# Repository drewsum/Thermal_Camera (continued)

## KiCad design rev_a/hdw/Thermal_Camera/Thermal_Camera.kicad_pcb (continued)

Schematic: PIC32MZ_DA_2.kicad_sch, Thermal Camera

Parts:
U1701: PIC32MZ2064DAR176; LQFP-176_20x20mm_P0.4mm_7p9x7p9mm_EP; Digi-Key PN PIC32MZ2064DAR176-I/2J-ND

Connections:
GLCD_B0: U1701.89 (GD16/EBID8/RPF5/SCL5/PMD8/RF5); also elsewhere on the board
GLCD_B1: U1701.97 (GD17/EBID9/RPF4/SDA5/PMD9/RF4); also elsewhere on the board
GLCD_B2: U1701.146 (GD18/EBIBS1/RJ10); also elsewhere on the board
GLCD_B3: U1701.130 (GD19/EBIA21/RK7); also elsewhere on the board
GLCD_B4: U1701.151 (GD20/EBIA22/RJ3); also elsewhere on the board
GLCD_B5: U1701.92 (GD21/EBIA23/RH15); also elsewhere on the board
GLCD_B7: U1701.137 (GD23/EBIA16/RK0); also elsewhere on the board
GLCD_G0: U1701.143 (GD8/EBID11/PMD11/RJ14); also elsewhere on the board
GLCD_G1: U1701.145 (GD9/EBIBS0/RJ12); also elsewhere on the board
GLCD_G4: U1701.134 (GD12/EBIA17/RK3); also elsewhere on the board
GLCD_G5: U1701.133 (GD13/EBIA18/RK4); also elsewhere on the board
GLCD_G6: U1701.132 (GD14/EBIA19/RK5); also elsewhere on the board
GLCD_G7: U1701.131 (GD15/EBIA20/RK6); also elsewhere on the board
GLCD_GCLK: U1701.148 (GCLK/EBICS2/RJ6); also elsewhere on the board
GLCD_GEN: U1701.147 (GEN/EBICS3/RJ7); also elsewhere on the board
GLCD_HSYNC: U1701.149 (HSYNC/EBICS1/RJ5); also elsewhere on the board
GLCD_R0: U1701.144 (GD0/EBID13/PMD13/RJ13); also elsewhere on the board
GLCD_R3: U1701.96 (GD3/EBIA8/RPG0/PMA8/RG0); also elsewhere on the board
GLCD_R4: U1701.95 (GD4/EBIA9/RPG1/PMA9/RG1); also elsewhere on the board
GLCD_R5: U1701.90 (GD5/EBIA10/RPF1/PMA10/RF1); also elsewhere on the board
GLCD_R6: U1701.91 (GD6/EBIA11/RPF0/PMA11/RF0); also elsewhere on the board
GLCD_VSYNC: U1701.150 (VSYNC/EBICS0/RJ4); also elsewhere on the board
LCD _CTP_RESET: U1701.112 (ETXD1/RJ9); also elsewhere on the board
LCD_CTP_INT: U1701.113 (ETXD0/RJ8); also elsewhere on the board
LCD_ENABLE: U1701.111 (ERXCLK/EREFCLK/RJ11); also elsewhere on the board
PGOOD_LED_SHDN: U1701.106 (ECOL/RH10); also elsewhere on the board
POS1P2_PGOOD: U1701.105 (ECRS/RH12); also elsewhere on the board
POS1P2_RUN: U1701.104 (ERXDV/ECRSDV/RH13); also elsewhere on the board
POS1P8_PGOOD: U1701.139 (EBIA4/AN36/PMA4/RH7); also elsewhere on the board
POS2P8_PGOOD: U1701.108 (ERXD0/RH8); also elsewhere on the board
POS2P8_RUN: U1701.107 (ERXD3/RH9); also elsewhere on the board
POS3P0_PGOOD: U1701.101 (ERXD2/RH6); also elsewhere on the board
POS12_PGOOD: U1701.100 (ERXD1/RH5); also elsewhere on the board
SDHC_SDDATA0: U1701.64 (TRD0/SDDATA0/SQID0/RG13); also elsewhere on the board
SDHC_SDDATA1: U1701.56 (TRD1/SDDATA1/SQID1/RG12); also elsewhere on the board
SDHC_SDDATA2: U1701.65 (TRD2/SDDATA2/SQID2/RG14); also elsewhere on the board
SD_PWR_EN: U1701.34 (AN21/RG15); also elsewhere on the board
SD_SPI_MISO: U1701.31 (AN13/C1INC/RPG7/SDA4/RG7); also elsewhere on the board
SD_SPI_MOSI: U1701.32 (AN30/C2IND/RPG8/SCL4/RG8); also elsewhere on the board
SD_SPI_SCK: U1701.30 (AN14/C1IND/SCK2/RG6); also elsewhere on the board
~SDHC_SDWP: U1701.141 (SDWP/EBIRP/RH2); also elsewhere on the board
~SD_SPI_CS: U1701.33 (EBIA2/AN23/C2INC/RPG9/PMA2/RG9); also elsewhere on the board

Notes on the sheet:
GLCD_G7
GPIO
GLCD_GEN
GLCD_VSYNC
GLCD_B0
GLCD_R6
GLCD_G0
SDDATA0
GLCD_HSYNC
GLCD_B4
GLCD_GCLK
GLCD_G6
SDDATA2
GLCD_B5
GLCD_R0
GLCD_B1
SDI2
GLCD_G4
GLCD_R3
GLCD_R4
SCK2
SDWP
See TABLE 36-1:RGB COLOR MAPPING for Graphic LCD Pin Mapping
SDDATA1
GLCD_G5
SDO2
GLCD_R5
GLCD_B7
GLCD_B3
GLCD_G1
GLCD_B2

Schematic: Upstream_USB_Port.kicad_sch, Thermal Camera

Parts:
C2601, C2603, C2605: 10uF; C_0402; Voltage 10V; Digi-Key PN 490-GRM155R61A106ME11DCT-ND
C2602: 0.1uF; C_0402; Voltage 50V; Digi-Key PN 490-10697-1-ND
C2604, C2606: 22pF; C_0402; Voltage 50V; Digi-Key PN 490-5868-1-ND
C2607: 10uF; C_1206; Voltage 25V; Digi-Key PN 399-8153-1-ND
J2601: USB_B_Mini; USB_Mini-B; Digi-Key PN 732-2109-1-ND
R2601: 10k; R_0402; Tolerance 1%; Digi-Key PN RMCF0402FT10K0CT-ND
R2602, R2603: 27; R_0402; Tolerance 1%; Digi-Key PN RMCF0402FT27R0CT-ND
R2604: 3.57k; R_0402; Tolerance 1%; Digi-Key PN RMCF0402FT3K57CT-ND
R2605: 1.15k; R_0402; Tolerance 1%; Digi-Key PN RMCF0402FT1K15CT-ND
R2606: 1.5k; R_0402; Tolerance 1%; Digi-Key PN RMCF0402FT1K50CT-ND
TP2601, TP2602: TP; Test_Point
U2601: TPS7A92; Texas_S-PDSO-N10_EP1.2x2mm; Digi-Key PN TPS7A9201DSKR
U2602: TPD3S044DBVR; SOT-23-6; Digi-Key PN 296-38836-1-ND

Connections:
+3.3V_USB: C2603.1, C2605.1, R2601.1, R2604.1, R2606.1, TP2601.1 (TP), U2601.1 (OUT), U2601.2 (OUT); also elsewhere on the board
+5V_USB: C2601.1, C2607.1, TP2602.1 (TP), U2601.7 (EN), U2601.9 (IN), U2601.10 (IN), U2602.4 (OUT); also elsewhere on the board
/Upstream USB Port/UFP_USB_CONN_USB+: J2601.3 (D+), R2602.1
/Upstream USB Port/UFP_USB_CONN_USB-: J2601.2 (D-), R2603.1
CHASSIS: J2601.6 (Shield)
GND: C2601.2, C2602.2, C2603.2, C2604.2, C2605.2, C2606.2, C2607.2, J2601.5 (GND), R2605.2, U2601.4 (GND), U2601.6 (SS_CTRL), U2601.11 (GND), U2602.2 (GND); also elsewhere on the board
unnamed: J2601.1 (VBUS), U2602.1 (EN), U2602.3 (IN)
unnamed: R2604.2, R2605.1, U2601.3 (FB)
unnamed: C2602.1, U2601.8 (NR/SS)
POS3P3_USB_PGOOD: R2601.2, U2601.5 (PG); also elsewhere on the board
UFP_USB_D+: C2604.1, R2602.2, R2606.2, U2602.6 (D1); also elsewhere on the board
UFP_USB_D-: C2606.1, R2603.2, U2602.5 (D2); also elsewhere on the board

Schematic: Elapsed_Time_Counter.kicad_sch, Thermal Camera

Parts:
C2301, C2302, C2303: 10uF; C_0402; Voltage 10V; Digi-Key PN 490-GRM155R61A106ME11DCT-ND
C2304, C2305: 0.1uF; C_0402; Voltage 50V; Digi-Key PN 490-10697-1-ND
D2301: BAT48JFILM; D_SOD-323; Digi-Key PN 497-5711-1-ND
DOC2301: 0x6B
DOC2302: 0x1F
U2301: DS1683; SOIC-8_3.9x4.9mm_Pitch1.27mm; Digi-Key PN DS1683S+-ND
U2302: MCP9804; DFN-8-1EP_3x2mm_P0.5mm_EP1.3x1.5mm; Digi-Key PN MCP9804T-E/MCCT-ND

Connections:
+3.0V: C2305.1, D2301.2 (A), U2301.1 (EVENT), U2302.5 (A2), U2302.6 (A1), U2302.7 (A0), U2302.8 (V_{DD}); also elsewhere on the board
GND: C2301.2, C2302.2, C2303.2, C2304.2, C2305.2, U2301.4 (GND), U2302.4 (GND), U2302.9 (EP/GND); also elsewhere on the board
I2C_SCL: U2301.5 (SCL), U2302.2 (SCL); also elsewhere on the board
I2C_SDA: U2301.6 (SDA), U2302.1 (SDA); also elsewhere on the board
unnamed: C2301.1, C2302.1, C2303.1, C2304.1, D2301.1 (K), U2301.8 (VCC)

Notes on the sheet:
Ambient, place away from power components

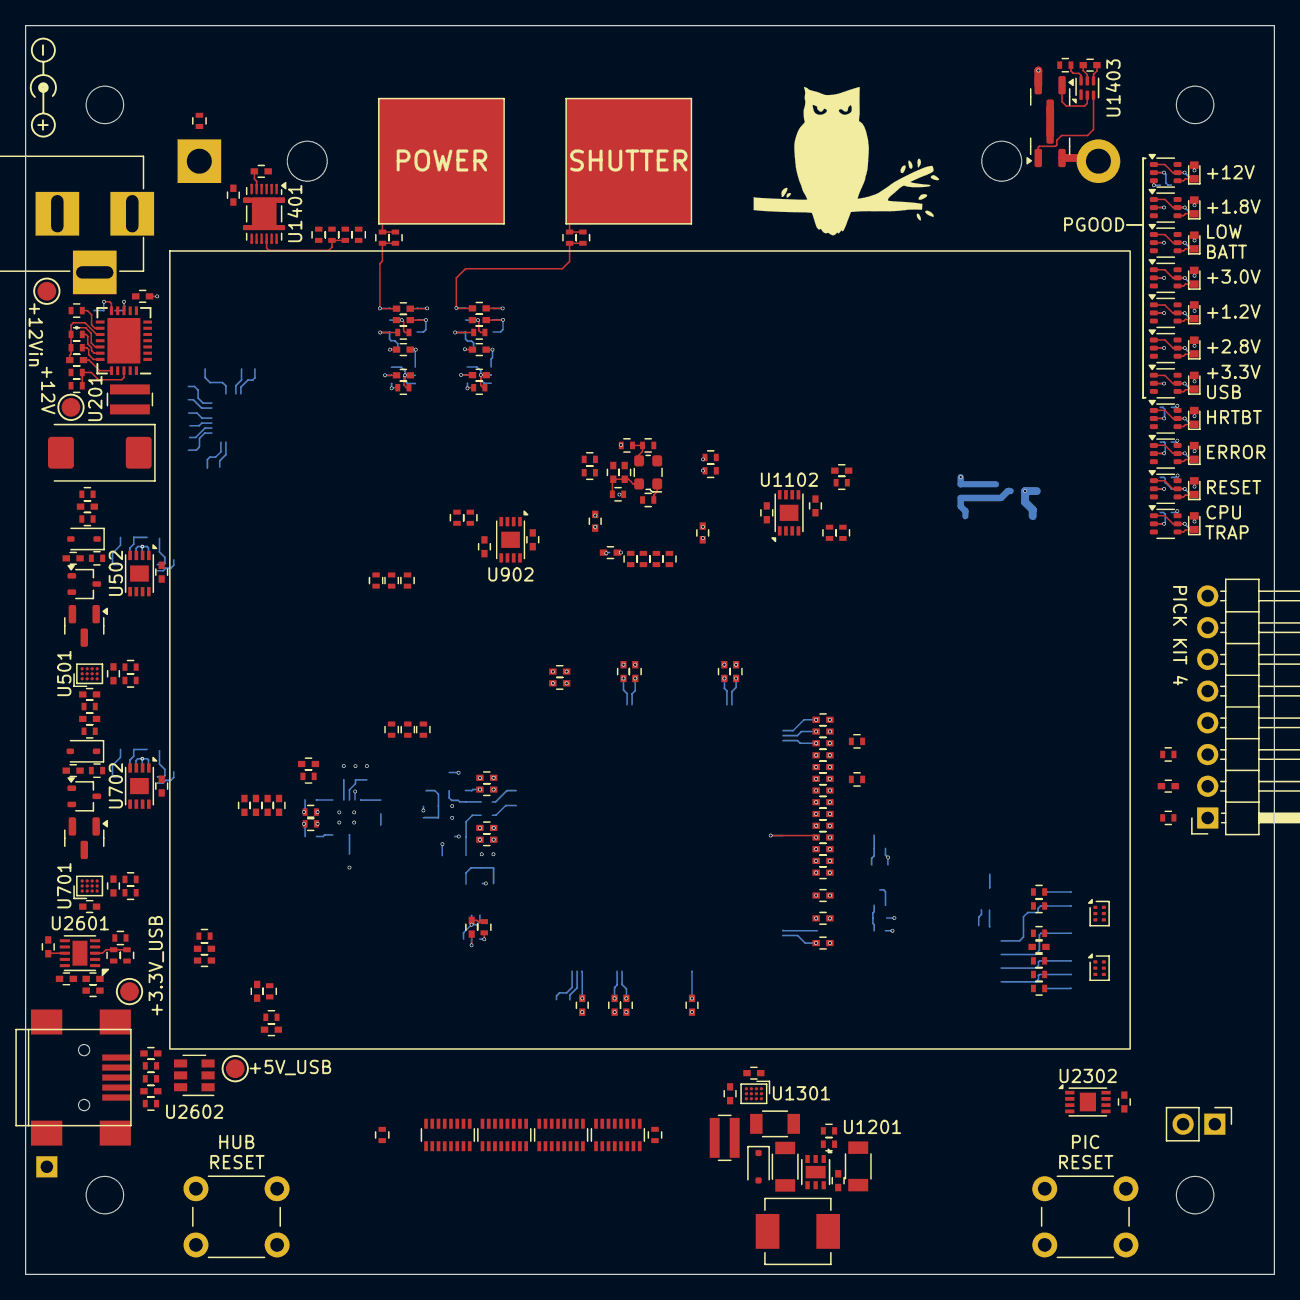
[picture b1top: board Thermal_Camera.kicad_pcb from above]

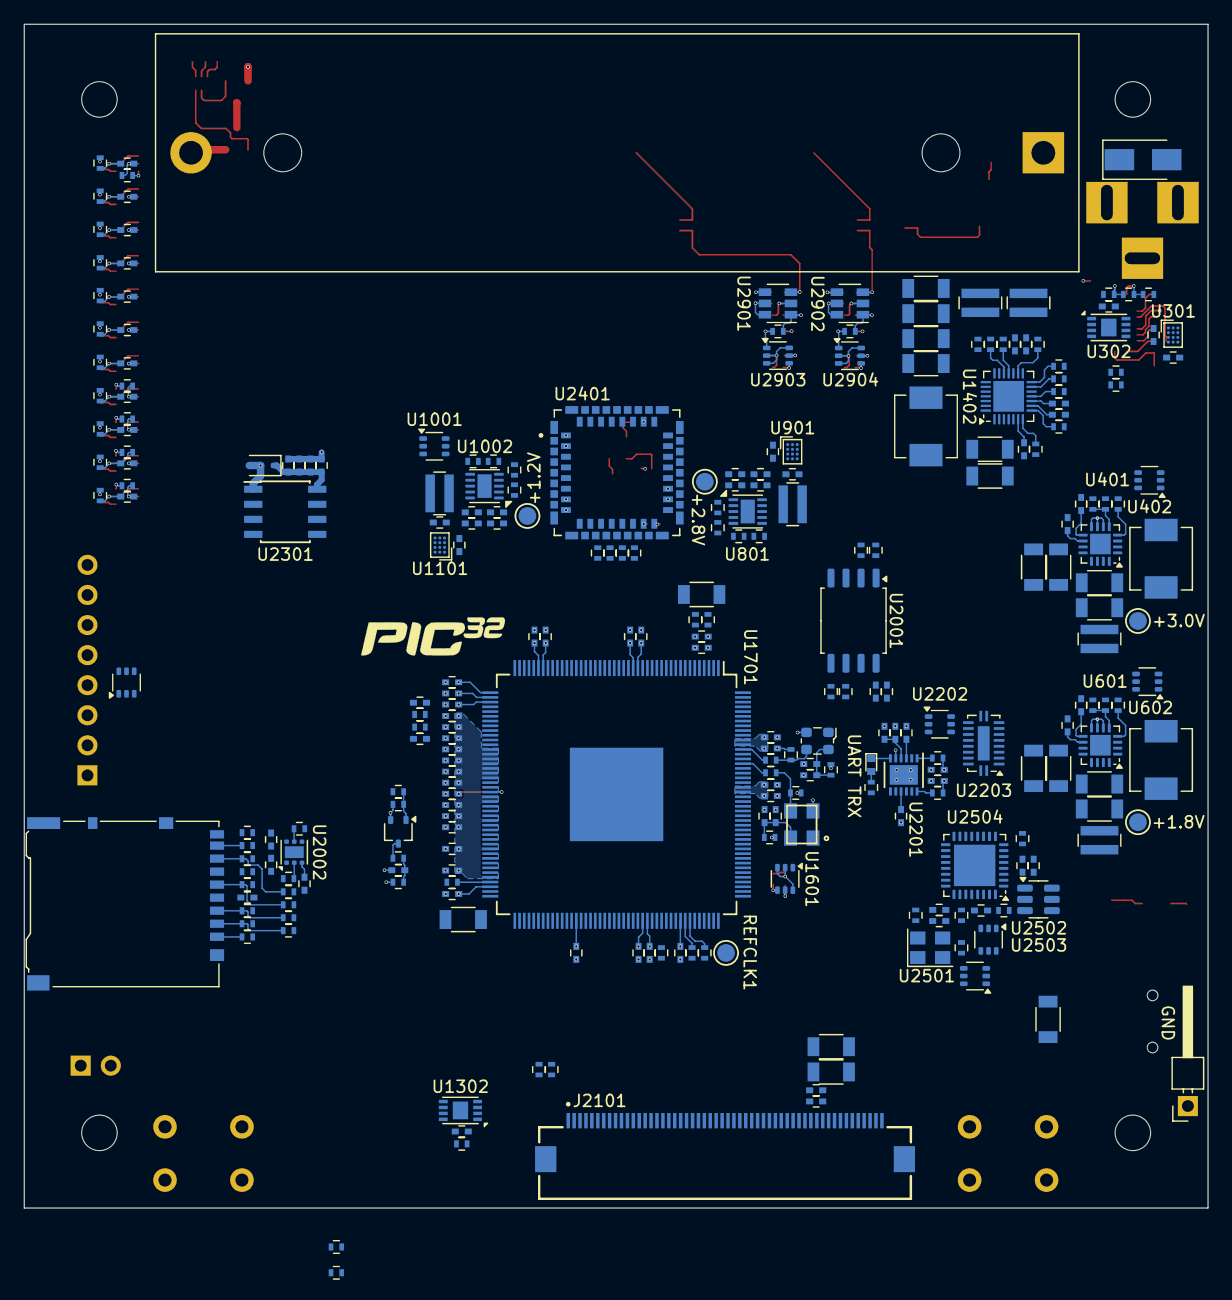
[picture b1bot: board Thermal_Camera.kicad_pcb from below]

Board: 8 copper layers, 100.0 x 100.0 mm, 512 parts (271 on the bottom side), 271 nets.

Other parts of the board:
C2901, C2902: 10nF; C_0402
C2903, C2904, C2907, C2908: 0.1uF; C_0402
C2905, C2906: 10uF; C_0402
H3001, H3002, H3003, H3004: MountingHole; MountingHole_3mm
R2901, R2902, R2903, R2904: 1k; R_0402
R2905, R2906, R2907, R2908, R2909, R2910: 10k; R_0402
SW2901, SW2902: Cap_Touch; Capacitive_Touch_Pad
U2901, U2902: AT42QT1010-TSHR; SOT-23-6
U2903, U2904: 74LVC1G97; SOT-363_SC-70-6

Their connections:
+3.0V: C2903.1, C2904.1, C2907.1, C2908.1, U2901.5 (VDD), U2901.6 (SYNC), U2902.5 (VDD), U2902.6 (SYNC), U2903.5 (VCC), U2904.5 (VCC); also elsewhere on the board
Cap_Touch_Power: R2909.1, U2903.4; also elsewhere on the board
Cap_Touch_Shutter: R2910.1, U2904.4; also elsewhere on the board
GND: C2903.2, C2904.2, C2905.2, C2906.2, C2907.2, C2908.2, R2905.2, R2906.2, R2909.2, R2910.2, U2901.2 (VSS), U2902.2 (VSS), U2903.2 (GND), U2903.3 (GND), U2903.6 (GND), U2904.2 (GND), U2904.3 (GND), U2904.6 (GND); also elsewhere on the board
unnamed: C2905.1, R2907.1, U2903.1
unnamed: C2906.1, R2908.1, U2904.1
unnamed: R2901.1, R2902.1, SW2901.1 (TP)
unnamed: R2903.1, R2904.1, SW2902.1 (TP)
unnamed: R2905.1, R2907.2, U2901.1 (OUT)
unnamed: C2901.1, U2901.4 (SNS)
unnamed: C2901.2, R2901.2, R2902.2, U2901.3 (SNSK)
unnamed: R2906.1, R2908.2, U2902.1 (OUT)
unnamed: C2902.1, U2902.4 (SNS)
unnamed: C2902.2, R2903.2, R2904.2, U2902.3 (SNSK)

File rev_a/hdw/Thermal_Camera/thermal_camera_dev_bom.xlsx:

Reference | Value | Qty | Configuration | Digi-Key PN | display_footprint
BT1401 | 18650 Cell | 1 |  | 1568-1488-ND
C201,C405,C605,C1707,C1708,C1709,C1710,C1711,C1712,C1720,C1721,C1722,C1723,C172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 | 10nF | 69 |  | 445-12201-1-ND | 402
C202,C401,C406,C601,C606,C803,C1001,C1004,C1405,C1407,C1414,C1501,C1502,C1601,C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 | 0.1uF | 87 |  | 490-10697-1-ND | 402
C203 | 100uF | 1 |  | 718-1102-1-ND | 7343
C301,C302,C303,C501,C502,C503,C701,C702,C703,C901,C902,C903,C1101,C1102,C1103,C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 | 0.1uF | 19 | Telemetry | 490-10697-1-ND | 402
C402,C404,C407,C408,C602,C604,C607,C608,C1201,C1203,C1204,C1402,C1404,C1409,C14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 | 10uF | 22 |  | 399-8153-1-ND | 1206
C403,C603,C801,C802,C804,C805,C1002,C1003,C1005,C1006,C1403,C1406,C1604,C1605,C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 | 10uF | 29 |  | 490-GRM155R61A106ME11DCT-ND | 402
C1202,C1401,C1408,C1411 | 1uF | 4 |  | 311-1439-1-ND | 402
C1719,C1726,C2208,C2209 | 47pF | 4 |  | 490-5942-1-ND | 402
C2301,C2302,C2303 | 10uF | 3 | ETC | 490-GRM155R61A106ME11DCT-ND | 402
C2304 | 0.1uF | 1 | ETC | 490-10697-1-ND | 402
C2604,C2606 | 22pF | 2 |  | 490-5868-1-ND | 402
D401,D601 | BAT48JFILM | 2 |  | 497-5711-1-ND
D1201 | PMEG6010CEJ | 1 |  | 1727-3882-1-ND
D1501 | PESD3V3L5UY | 1 |  | 1727-3828-1-ND
D2001,D2002 | PESD3V3L4UF | 2 |  | 1727-5789-1-ND
D2201 | Yellow | 1 |  | VLMY1500-GS08CT-ND
D2301 | BAT48JFILM | 1 | ETC | 497-5711-1-ND
D2701,D2702,D2704,D2705,D2706,D2707,D2709,D2801 | Green | 8 |  | 1497-1219-1-ND
D2703,D2708,D2802,D2803,D2804 | Red | 5 |  | VLMS1500-GS08CT-ND
J1401 | 18650 Holder | 1 |  | BK-18650-PC2-ND
J2001 | Micro_SD_Card_Det_Hirose_DM3AT | 1 |  | HR1964CT-ND
J2101 | LCD Pixel Data | 1 |  | 2073-FFC2B35-54-GCT-ND
J2102 | LCD CTP Data | 1 |  | 2073-FFC2B35-06-GCT-ND
J2601 | USB_B_Mini | 1 |  | 732-2109-1-ND
L401,L601 | 2.2uH | 2 |  | 541-1236-1-ND | IHLP2020
L1201 | 22uH | 1 |  | 541-1243-1-ND | IHLP2020
L1401 | 4.7uH | 1 |  | 541-1222-1-ND | IHLP2020
L1501,L1502,L1601,L1602,L1701,L1702,L2401,L2501 | 600R 0.5A | 8 |  | 490-5441-1-ND
N201 | +12V 1A Power Supply | 1 |  | 993-1335-ND
N2101 | LCD Module | 1 |  | GLT035320240IS1-CTP
N2401 | Lepton3.5 Sensor | 1 |  | 500-0771-01-ND
Q401,Q601,Q1501 | BSS214NW | 3 |  | BSS214NWH6327XTSA1CT-ND
Q402,Q602 | ZXMS6004FFTA | 2 |  | ZXMS6004FFCT-ND
Q1401,Q1402 | DMN3042L | 2 |  | DMN3042L-7DICT-ND
R201 | 51.1k | 1 |  | RMCF0402FT51K1CT-ND | 402
R202,R209,R409,R807,R2605 | 1.15k | 5 |  | RMCF0402FT1K15CT-ND | 402
R203,R208 | 5.11k | 2 |  | RMCF0402FT5K11CT-ND | 402
R204,R206,R211,R402,R403,R404,R602,R603,R604,R801,R802,R1001,R1002,R1003,R1201,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 | 10k | 72 |  | RMCF0402FT10K0CT-ND | 402
R205,R210,R405,R407,R605,R607,R803,R805,R1004,R1006,R1204,R1206 | 10 | 12 | Telemetry | RMCF0402FT10R0CT-ND | 402
R207,R406,R606,R804,R1005,R1205,R1412,R1413 | 0.02 | 8 |  | P16010CT-ND | 612
R401,R601,R1202,R1203,R1501,R1503,R1605,R1606,R2001,R2002,R2003,R2004,R2005,R20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 | 10 | 26 |  | RMCF0402FT10R0CT-ND | 402
R408 | 3.16k | 1 |  | RMCF0402FT3K16CT-ND | 402
R608 | 1.87k | 1 |  | RMCF0402FT1K87CT-ND | 402
R609,R2606 | 1.5k | 2 |  | RMCF0402FT1K50CT-ND | 402
R806 | 2.87k | 1 |  | RMCF0402FT2K87CT-ND | 402
R1007,R1406 | 5.9k | 2 |  | RMCF0402FT5K90CT-ND | 402
R1008 | 11.8k | 1 |  | RMCF0402FT11K8CT-ND | 402
R1401,R1403 | 10K | 2 |  | RMCF0402FT10K0CT-ND | 402
R1402 | 1.8M | 1 |  | RMCF0402FT1M80CT-ND | 402
R1404,R1405,R1408,R1409 | 100k | 4 |  | RMCF0402FT100KCT-ND | 402
R1411 | 1.2k | 1 |  | RMCF0402FT1K20CT-ND | 402
R1414 | 2.2k | 1 |  | RMCF0402FT2K20CT-ND | 402
R1415 | 330 | 1 |  | RMCF0402FT330RCT-ND | 402
R1505,R2201,R2702,R2703,R2704,R2705,R2706,R2707,R2708,R2709,R2710,R2803,R2804,R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 | 1k | 19 |  | RMCF0402FT1K00CT-ND | 402
R1701,R1702,R2203,R2204,R2602,R2603 | 27 | 6 |  | RMCF0402FT27R0CT-ND | 402
R1703,R1704,R2205,R2206 | 15k | 4 |  | RMCF0402FT15K0CT-ND | 402
R2604 | 3.57k | 1 |  | RMCF0402FT3K57CT-ND | 402
RN2101,RN2102,RN2103,RN2104 | 10k | 4 |  | Y1103CT-ND
TH1401,TH1402 | 10k | 2 |  | 445-174911-1-ND | 402
TP202,TP203,TP401,TP601,TP801,TP1001,TP1601,TP2601,TP2602 | TP | 9
U201 | TPS26600RHFT | 1 |  | 296-45478-1-ND
U301,U501,U701,U901,U1101,U1301 | INA231A | 6 | Telemetry | 296-41263-1-ND
U302,U502,U702,U902,U1102,U1302,U2302 | MCP9804 | 7 | Telemetry | MCP9804T-E/MCCT-ND
U401,U601,U1001,U1601,U2202,U2501,U2503,U2701,U2702,U2703,U2704,U2705,U2706,U27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 | 74LVC1G97 | 20 |  | 296-15582-1-ND
U402,U602 | TPS62130A | 2 |  | 296-39446-1-ND
U801,U1002,U2601 | TPS7A92 | 3 |  | TPS7A9201DSKR
U1201 | DIO5661CD6 | 1 |  | N/A
U1401 | BQ27441DRZT-G1A | 1 |  | 296-37271-1-ND
U1402 | MAX8903G | 1 |  | MAX8903GETI+-ND
U1403 | BQ29700 | 1 |  | 296-43985-1-ND
U1701 | PIC32MZ2064DAR176 | 1 |  | PIC32MZ2064DAR176-I/2J-ND
U2001 | SST25VF080B-50-4x-S2Ax | 1 |  | SST25VF080B-50-4C-S2AF-ND
U2002 | TPS22810DRV | 1 |  | 296-47868-1-ND
U2201 | FT234XD | 1 |  | 768-1178-1-ND
U2203 | FXMA108 | 1 |  | FXMA108BQX
U2301 | DS1683 | 1 | ETC | DS1683S+-ND
U2401 | FLIR_Lepton3p5_Socket | 1 |  | 1050281001
U2502 | TPS3808G33 | 1 |  | 296-17195-1-ND
U2504 | TUSB2046BIRHBT | 1 |  | 296-27130-1-ND
U2602 | TPD3S044DBVR | 1 |  | 296-38836-1-ND
U2708,U2709 | 74LVC1G97 | 2 |  | 296-15582-1-ND
U2901,U2902 | AT42QT1010-TSHR | 2 |  | AT42QT1010-TSHRCT-ND
X1601 | ECS-2520MV-240-BN | 1 |  | XC2750CT-ND
X1602 | ECS-327KE | 1 |  | XC1751CT-ND
X2401 | ECS-2520MV-250-CN | 1 |  | XC2752CT-ND
X2501 | ASE-48.000MHz | 1 |  | 535-ASE-48.000MHZ-L-C-TCT-ND

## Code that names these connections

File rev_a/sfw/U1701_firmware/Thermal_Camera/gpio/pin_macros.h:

/* ************************************************************************** */
/** Descriptive File Name

  @Company
 Drew Maatman

  @File Name
    pin_macros.h

  @Summary
    Macros for setting and checking the state of GPIO pins

  @Description
    Macros for setting and checking the state of GPIO pins
 */
/* ************************************************************************** */

#ifndef _PIN_MACROS_H    /* Guard against multiple inclusion */
#define _PIN_MACROS_H

#include <xc.h>

#define HIGH    1
#define LOW     0

// These pin macros allow for easier manipulation of GPIO with matching
// signal names from the hardware schematic

// Port A
#define POS3P3_USB_PGOOD_PIN        PORTAbits.RA2
// The board silkscreen for these two cap-touch pads is swapped relative to
// the schematic net names (RA9/RA10 themselves are correct, unchanged) --
// these macros are intentionally cross-mapped so their names match what's
// printed on the board (and therefore what the user actually presses),
// not the net name in the schematic/netlist. Do not "fix" this back to
// RA9=SHUTTER/RA10=POWER without first confirming the silkscreen has been
// corrected in hardware.
#define CAP_TOUCH_SHUTTER_PIN       PORTAbits.RA10
#define CAP_TOUCH_POWER_PIN         PORTAbits.RA9
#define SD_CARD_DETECT_PIN          PORTAbits.RA0

// Port B
#define nFLASH_SPI_CS_PIN           LATBbits.LATB4
// RB5 (BACKLIGHT_PWM net) has no plain digital pin macro: it's permanently
// owned by the OC3 peripheral (PPS-mapped in pic32mzda_gpio_setup.c) once
// application/backlight_pwm.c enables OC3 -- writing LATB5 directly has no
// effect afterward. Use BacklightPWM_SetBrightness() instead.
#define POS2P8_PGOOD_PIN            PORTBbits.RB8
#define FLIR_CLK_EN_PIN             LATBbits.LATB11
#define nFLASH_SPI_WP_PIN           LATBbits.LATB12
#define nFLIR_PWR_DWN_PIN           LATBbits.LATB13
#define POS2P8_RUN_PIN              LATBbits.LATB15

// Port C
#define POS12_PGOOD_PIN             PORTCbits.RC1
#define nBATT_CHG_PIN               PORTCbits.RC2
#define nBATT_DOK_PIN               PORTCbits.RC3
#define HEARTBEAT_LED_PIN           LATCbits.LATC4

// Port D
#define FLIR_VOSPI_VSYNC_PIN        PORTDbits.RD0
#define nFLIR_VOSPI_CS_PIN          LATDbits.LATD1
#define nFLIR_RESET_PIN             LATDbits.LATD15

// Port E
#define nBATT_FLT_PIN               PORTEbits.RE0
#define nBATT_UOK_PIN               PORTEbits.RE1
#define RESET_LED_PIN               LATEbits.LATE4
#define nBATT_CEN_PIN               LATEbits.LATE6
#define BATT_IUSB_PIN               LATEbits.LATE7
#define BATT_LOWBATT_PIN            PORTEbits.RE8
#define PGOOD_LED_SHDN_PIN          LATEbits.LATE9

// Port F
#define CPU_TRAP_LED_PIN            LATFbits.LATF2
#define POS1P2_RUN_PIN              LATFbits.LATF12

// Port G
#define nSD_SPI_CS_PIN              LATGbits.LATG9
#define SD_PWR_EN_PIN               LATGbits.LATG15

// Port H
#define POS3P0_PGOOD_PIN            PORTHbits.RH3
#define POS1P2_PGOOD_PIN            PORTHbits.RH4
#define POS1P8_PGOOD_PIN            PORTHbits.RH7
#define ERROR_LED_PIN               LATHbits.LATH14

// Port J
#define LCD_CTP_INT_PIN             PORTJbits.RJ8
// LAT-side counterpart of LCD_CTP_INT_PIN: RJ8 is normally an input (the
// GT911 touch controller's interrupt line), but must be driven as a GPIO
// output during the one-time I2C-address-select sequence at boot
// (i2c/device_driver/gt911.c) -- TRISJ is switched to output for that
// window only, then restored to input.
#define LCD_CTP_INT_LAT_PIN         LATJbits.LATJ8
#define LCD_CTP_RESET_PIN           LATJbits.LATJ9
#define LCD_ENABLE_PIN              LATJbits.LATJ11

// Port K - No GPIO pins used

#endif /* _PIN_MACROS_H */

/* *****************************************************************************
 End of File
 */

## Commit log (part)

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2023-11-11 added kicad project
2023-11-11 Generated blank schematic
2023-11-11 copied lots of circuitry to reuse
2023-11-11 generated PDF
2023-11-12 added PIC32MZ DA pinout spreadsheet
2023-11-12 finished PIC32MZ DA symbol
2023-11-13 added lepton sensor, made some other schematic progress
2023-11-14 changed USB HS port to hub
2023-11-14 added many more blank schematic sheets
2023-11-14 added FLIR leptson IO level shifters
2023-11-15 added SPI Flash and SD Card
2023-11-16 added some power supplies
2023-11-16 fixed SOSC pin connection
2023-11-18 changed a lot of circuits from +3.3V to +3.0V VDD
2023-11-19 added new telemetry circuits
2023-11-20 duplicated telemetry for all rails, added random tweaks to logic levels of signals
2023-12-01 generated battery charger symbol
2023-12-01 added battery circuitry, LCD backlight
2023-12-05 added PIC32 bypass, SD card load switch, other random junk
2023-12-06 added some USB stuff
2023-12-06 added some more USB stuff
2023-12-07 added some LCD components
2023-12-07 added pull resistors for LCD signals
2023-12-07 changed LED backlight driver
2023-12-07 chose backlight boost inductor
2023-12-07 added notes for battery
2023-12-08 Added battery cell and protection IC
2024-03-29 lots of random schematic progress
2024-03-29 assigned some GPIO pins
2024-04-02 blah blah
2024-04-02 worked on some battery stuff
2024-04-03 some stuff
2024-05-25 lots of schematic progress
2024-05-25 assigned a ton of footprints
2024-05-25 assigned some part numbers
2024-05-25 assigned resistor part numbers
2024-05-25 hid passive refdes
2024-05-25 started arranging some parts
2024-05-25 more part grouping
2024-07-12 started placing a lot more components in PCB layout
2024-07-12 more PCB component placement
2024-07-16 lots of PCB placement progress
2024-07-19 fixed LCD ribbon cable pinout, added footprint
2024-08-15 generated rough LCD outline, made board outline
2024-08-15 placed input power circuit
2024-08-15 placed battery charger circuitry
2024-08-15 placed some power supplies
2024-08-15 placed more power supplies
2024-08-15 placed LCD backlight driver
2024-08-15 placed MCU
2024-08-15 finished placing components
2024-08-15 set up stackup, via sizes
2024-08-15 assigned some net classes
2024-08-15 some routing
2024-08-19 updated via geometries
2024-08-19 some random routing started
2024-08-19 a ton of routing progress, power planes, ehat have you
2024-08-30 some random routing
2024-08-30 many more routes
2024-08-30 more routing
2024-09-02 classed and routed some high speed single ended nets
2024-09-03 way more routing
2024-09-04 length matched some stuff on layer 6
2024-09-04 more layer 6 length matching
2024-09-04 escaped LCD signals
2024-09-05 some LCD routing
2024-09-05 more LCD routing
2024-09-05 length matched LCD signals
2024-09-05 some more routing, moved some misc nets on MCU
2024-09-06 more PCU pinout optimization
2024-09-06 random routing
2024-09-06 Even moar routing
2024-09-10 routed I2C
2024-09-10 more random LED routing
2024-09-15 assigned CTP connector footprint
2024-09-15 got unconnects near zero
2024-09-20 added some stitching caps
2024-09-24 added some more stitching caps
2024-10-11 generated gerbers, bom
2024-10-26 added interrupt list
2024-10-27 started working on interrupt control
2024-10-27 added framework for interrupt control
2024-11-10 generated firmware project
2024-11-10 added config file
2024-11-10 added vscode conversion
2024-11-10 defined pin macros
2024-11-10 Added PPS output mapping macros
2024-11-10 got GPIO setup working
2024-11-11 wrote interrupt code
2024-11-12 made temporary code changes to use FRC instead of POSC
2024-11-12 Assigned PPS pins
2024-11-12 working on heartbeat timer
2024-11-13 got heartbeat working
2024-11-13 added prefetch
2024-11-13 fixed heartbeat timer period
2024-11-13 added WDT
2024-11-13 added PMD
2024-11-14 fixed heartbeat timer period, again
2024-11-14 added REFCLK5 printouts
2024-11-14 working on UART, baud rate incorrect
2024-11-15 fixed clocking shit
2024-12-12 got serial working
2024-12-12 got cause of reset working
2024-12-12 attemping to fix serial receive
2024-12-14 fixed gitignoring of XML files, fuck
2024-12-17 adding netbeats XMLs
